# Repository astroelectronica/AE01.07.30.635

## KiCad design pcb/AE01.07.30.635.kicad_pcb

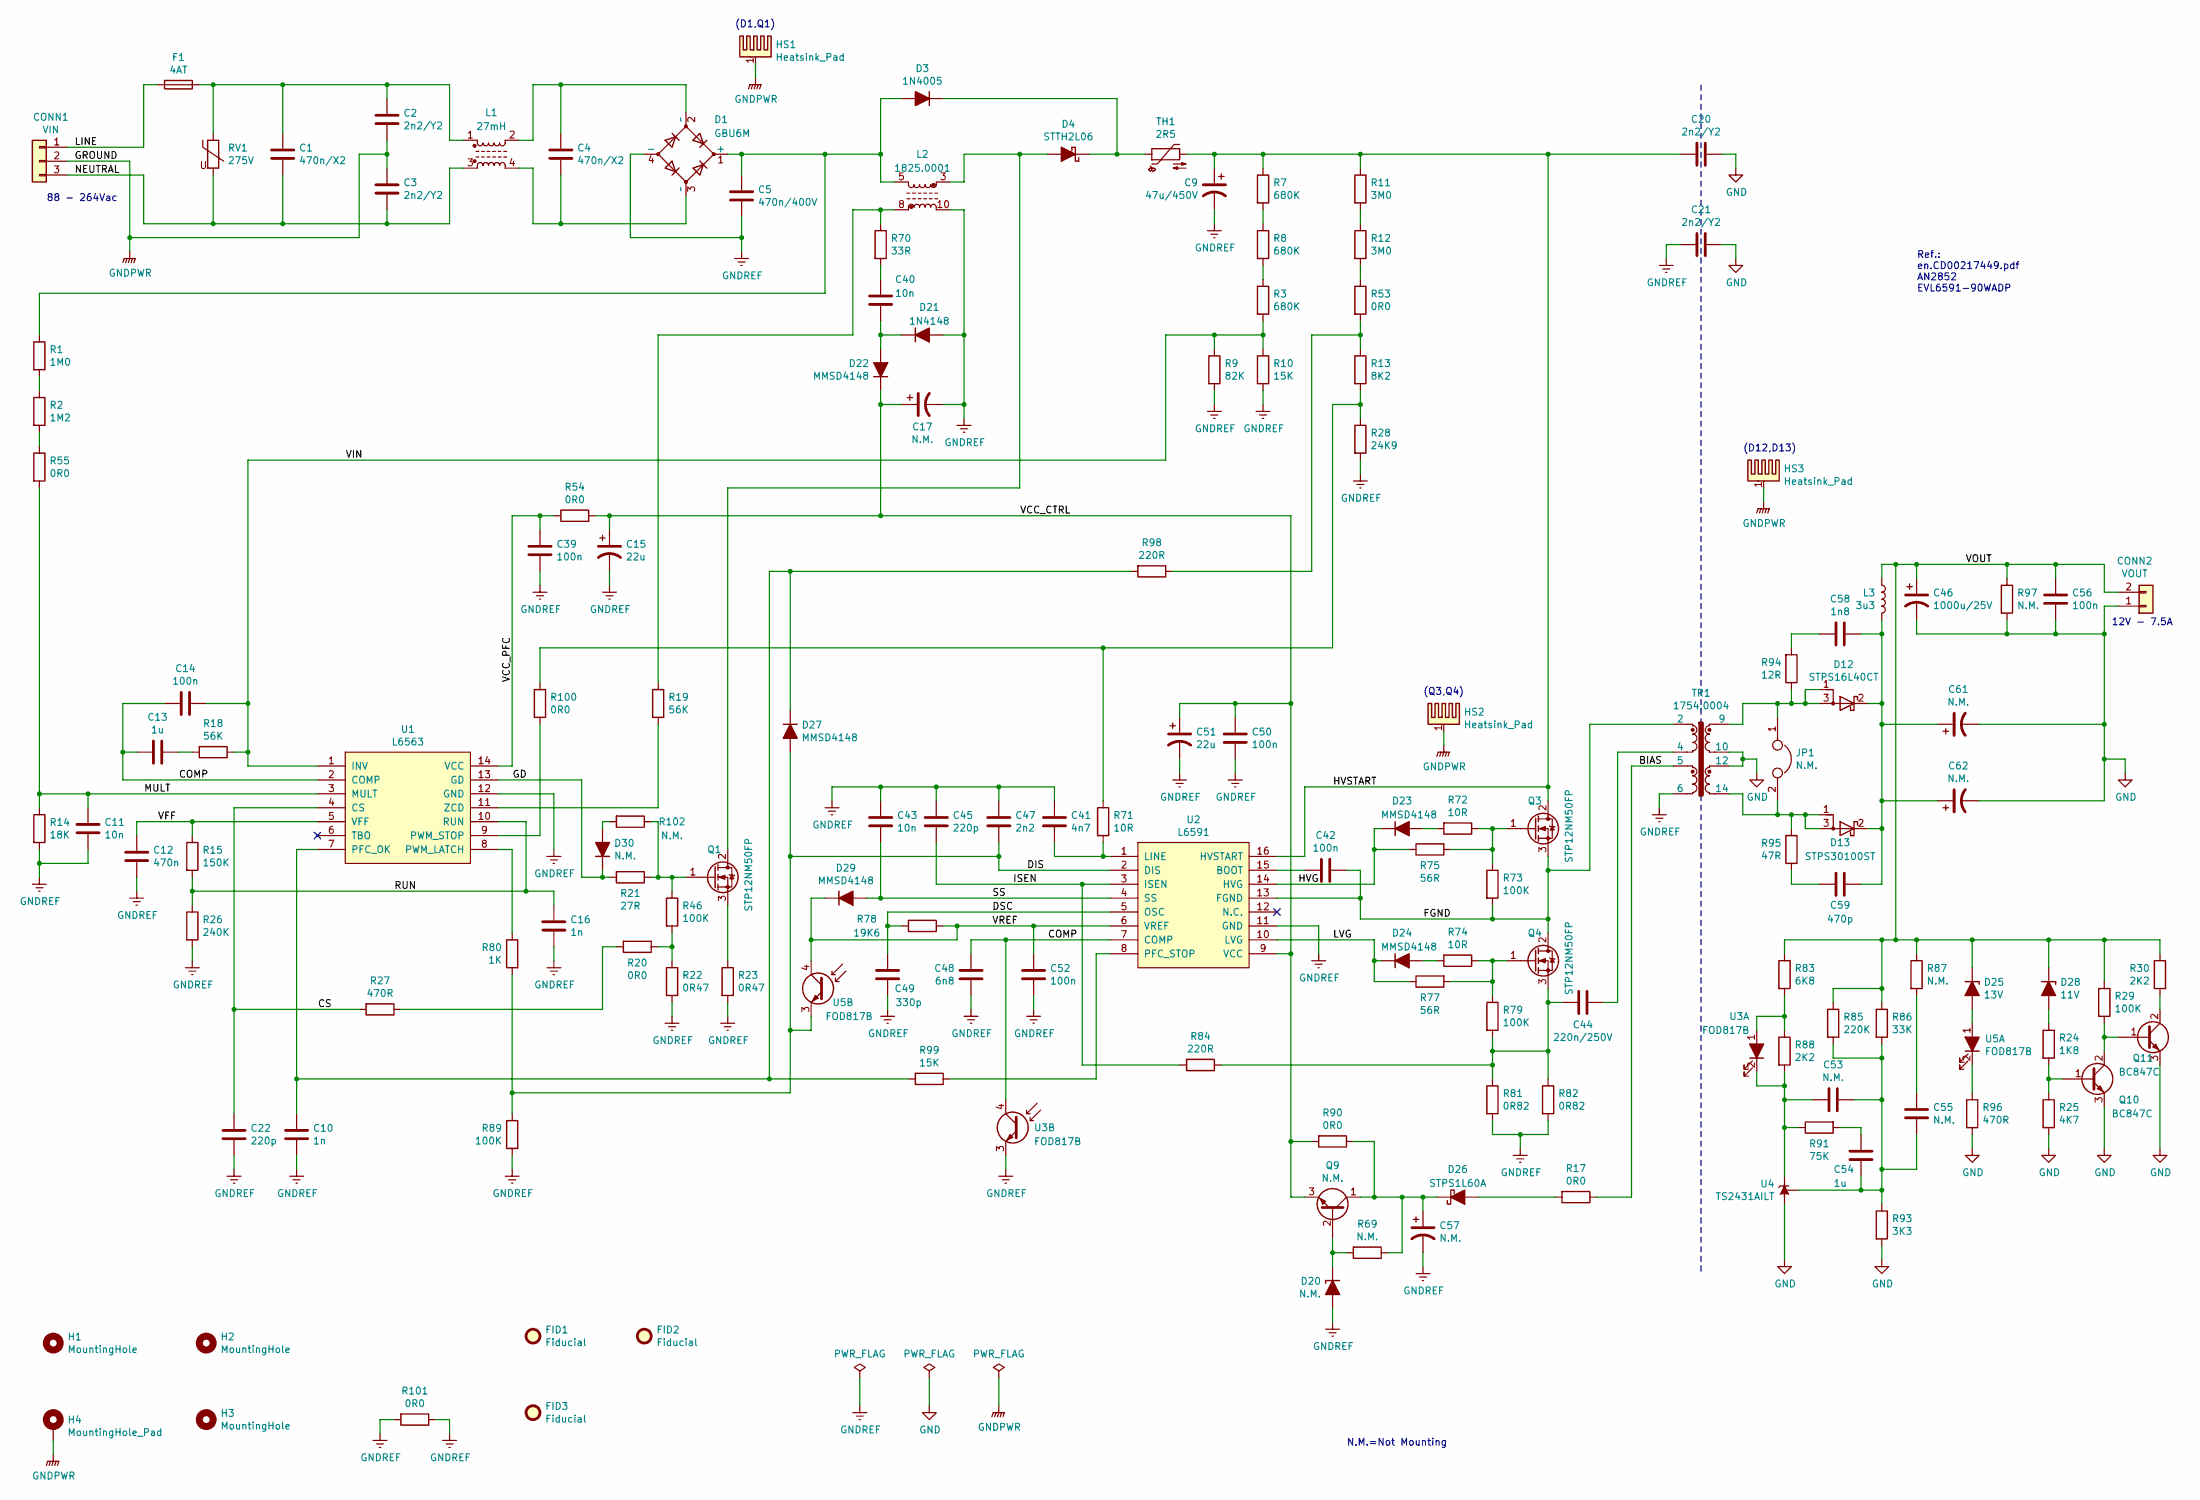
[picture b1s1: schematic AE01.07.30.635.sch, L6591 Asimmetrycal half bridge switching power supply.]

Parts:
C1, C4: 470n/X2; C_Rect_L18.0mm_W8.0mm_P15.00mm_FKS3_FKP3; MPN R46KI3470JH02M
C2, C3, C20, C21: 2n2/Y2; C_Disc_D8.0mm_W5.0mm_P7.50mm; MPN VY2222M31Y5VS63V7
C5: 470n/400V; C_Rect_L33.0mm_W13.0mm_P27.50mm_MKS4; MPN R76PR3470SE30J
C9: 47u/450V; CP_Radial_D18.0mm_P7.50mm; MPN EEU-ED2W470
C10, C16: 1n; C_0805_2012Metric; MPN C0805C102K5RACTU
C11, C40, C43: 10n; C_0805_2012Metric; MPN CC0805KRX7R9BB103
C12: 470n; C_0805_2012Metric; MPN CL21B474KAFNNNG
C13, C54: 1u; C_0805_2012Metric; MPN GCM21BR71E105KA56L
C14, C39, C42, C50, C52, C56: 100n; C_0805_2012Metric; MPN 08055C104KAT2A
C15, C51: 22u; CP_Radial_D5.0mm_P2.00mm; MPN UHE1H220MDD
C17, C57: N.M.; CP_Radial_D5.0mm_P2.00mm; MPN N.M.
C22, C45: 220p; C_0805_2012Metric; MPN C0805C221J5GACTU
C41: 4n7; C_0805_2012Metric; MPN CL21B472KB65PND
C44: 220n/250V; C_Rect_L18.0mm_W6.0mm_P15.00mm_FKS3_FKP3; MPN B32652A3224J000
C46: 1000u/25V; CP_Radial_D10.0mm_P5.00mm; MPN UVZ1E102MPD
C47: 2n2; C_0805_2012Metric; MPN CC0805KRX7R9BB222
C48: 6n8; C_0805_2012Metric; MPN CC0805KRX7R9BB682
C49: 330p; C_0805_2012Metric; MPN CC0805GRNPO9BN331
C53, C55: N.M.; C_0805_2012Metric; MPN N.M.
C58: 1n8; C_0805_2012Metric; MPN 08055C182KAT2A
C59: 470p; C_0805_2012Metric; MPN CC0805KRX7R9BB471
C61, C62: N.M.; CP_Radial_D10.0mm_P5.00mm; MPN N.M.
CONN1: VIN; TerminalBlock_Phoenix_MKDS-1,5-3-5.08_1x03_P5.08mm_Horizont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; MPN 1715734
CONN2: VOUT; TerminalBlock_Phoenix_MKDS-1,5-2-5.08_1x02_P5.08mm_Horizont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; MPN 1715721
D1: GBU6M; Diode_Bridge_Vishay_GBU; MPN GBU6M-E3/51
D3: 1N4005; D_DO-41_SOD81_P12.70mm_Horizontal; MPN 1N4005RLG
D4: STTH2L06; D_DO-41_SOD81_P12.70mm_Horizontal; MPN STTH2L06
D12: STPS16L40CT; TO-220-3_Vertical; MPN STPS16L40CT
D13: STPS30100ST; TO-220-3_Vertical; MPN STPS30100ST
D20, D30: N.M.; D_SOD-123; MPN N.M.
D21: 1N4148; D_DO-35_SOD27_P12.70mm_Horizontal; MPN 1N4148TR
D22, D23, D24, D27, D29: MMSD4148; D_SOD-123; MPN MMSD4148T1G
D25: 13V; D_SOD-123; MPN MMSZ5243C-E3-08
D26: STPS1L60A; D_SMA; MPN STPS2L60A
D28: 11V; D_SOD-123; MPN MMSZ5241C-E3-08
F1: 4AT; Fuseholder_TR5_Littelfuse_No560_No460; MPN 37214000411
FID1, FID2, FID3: Fiducial; Fiducial_0.5mm_Mask1mm
H1, H2, H3: MountingHole; MountingHole_3.2mm_M3_Pad_Via
H4: MountingHole_Pad; MountingHole_3.2mm_M3_Pad_Via
HS1, HS2, HS3: Heatsink_Pad
JP1: N.M.; PinHeader_1x02_P2.54mm_Vertical; MPN N.M.
L1: 27mH; Choke_Schaffner_RN142-04-33.1x32.5mm; MPN RN142-1.4-02-27M
L2: 1825.0001; RM14-LP_mF_1k_12-8_lo_rtg; MPN 1825.0001
L3: 3u3; L_Toroid_Vertical_L17.8mm_W9.7mm_P7.11mm_Pulse_B; MPN 2000-3R3-V-RC
Q1, Q3, Q4: STP12NM50FP; TO-220-3_Vertical; MPN STP12NM50FP
Q9: N.M.; SOT-23; MPN N.M.
Q10, Q11: BC847C; SOT-23; MPN BC847CLT1G
R1: 1M0; R_1206_3216Metric; MPN ERJ-8GEYJ105V
R2: 1M2; R_1206_3216Metric; MPN ERJ-8GEYJ125V
R3, R7, R8: 680K; R_Axial_DIN0204_L3.6mm_D1.6mm_P7.62mm_Horizontal; MPN MRS16000C6803FCT00
R9: 82K; R_0805_2012Metric; MPN RC0805FR-0782KL
R10: 15K; R_0805_2012Metric; MPN RC0805FR-0715KL
R11, R12: 3M0; R_Axial_DIN0414_L11.9mm_D4.5mm_P25.40mm_Horizontal; MPN HVR3700003004FR500
R13: 8K2; R_0805_2012Metric; MPN RC0805FR-078K2L
R14: 18K; R_1206_3216Metric; MPN ERJ-8GEYJ183V
R15: 150K; R_1206_3216Metric; MPN RK73B2BTTD154J
R17, R20, R53, R54, R55, R90, R100, R101: 0R0; R_1206_3216Metric; MPN RC1206JR-070RL
R18, R19: 56K; R_0805_2012Metric; MPN RC0805FR-0756KL
R21: 27R; R_1206_3216Metric; MPN RC1206JR-0727RL
R22, R23: 0R47; R_Axial_DIN0207_L6.3mm_D2.5mm_P15.24mm_Horizontal; MPN NFR25H0004707JR500
R24: 1K8; R_0805_2012Metric; MPN RC0805FR-071K8L
R25: 4K7; R_0805_2012Metric; MPN RC0805FR-074K7L
R26: 240K; R_0805_2012Metric; MPN ERJ-6ENF2403V
R27, R96: 470R; R_1206_3216Metric; MPN RC1206JR-07470RL
R28: 24K9; R_0805_2012Metric; MPN RC0805FR-0724K9L
R29, R46, R73, R79: 100K; R_0805_2012Metric; MPN RC0805FR-07100KL
R30: 2K2; R_1206_3216Metric; MPN RC1206FR-072K2L
R69, R87, R102: N.M.; R_0805_2012Metric; MPN N.M.
R70: 33R; R_1206_3216Metric; MPN RC1206FR-0733RL
R71: 10R; R_1206_3216Metric; MPN ERJ-8ENF10R0V
R72, R74: 10R; R_0805_2012Metric; MPN RMCF0805FT10R0
R75, R77: 56R; R_0805_2012Metric; MPN RC0805FR-0756RL
R78: 19K6; R_0805_2012Metric; MPN RC0805FR-0719K6L
R80: 1K; R_0805_2012Metric; MPN RC0805FR-071KL
R81, R82: 0R82; R_1206_3216Metric; MPN RL1206FR-070R82L
R83: 6K8; R_0805_2012Metric; MPN RC0805FR-076K8L
R84, R98: 220R; R_1206_3216Metric; MPN RC1206FR-07220RL
R85: 220K; R_0805_2012Metric; MPN RC0805FR-07220KL
R86: 33K; R_0805_2012Metric; MPN RC0805FR-0733KL
R88: 2K2; R_0805_2012Metric; MPN RC0805FR-072K2L
R89: 100K; R_1206_3216Metric; MPN RC1206FR-07100KL
R91: 75K; R_0805_2012Metric; MPN RC0805FR-0775KL
R93: 3K3; R_0805_2012Metric; MPN RC0805FR-073K3L
R94: 12R; R_1206_3216Metric; MPN RC1206FR-0712RL
R95: 47R; R_1206_3216Metric; MPN RC1206FR-0747RL
R97: N.M.; R_1206_3216Metric; MPN N.M.
R99: 15K; R_1206_3216Metric; MPN RC1206FR-0715KL
RV1: 275V; RV_Disc_D15.5mm_W5.4mm_P7.5mm; MPN B72214S2271K151
TH1: 2R5; C_Disc_D16.0mm_W5.0mm_P7.50mm; MPN B57237S0259M000
TR1: 1754.0004; ETD34_lr_h14_-1_rtg; MPN 1754.0004
U1: L6563; SOIC-14_3.9x8.7mm_P1.27mm; MPN L6563S
U2: L6591; SOIC-16_3.9x9.9mm_P1.27mm; MPN L6591TR
U3, U5: FOD817B; DIP-4_W7.62mm; MPN FOD817B
U4: TS2431AILT; SOT-23; MPN TS2431AILT

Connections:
/BIAS: R17.1, TR1.5
/COMP: C13.2, C14.2, C48.1, U1.2 (COMP), U2.7 (COMP), U3.4
/CS: C22.1, R27.2, U1.4 (CS)
/DIS: C47.2, D27.2 (A), R80.2, R89.1, U2.2 (DIS), U5.3
/DSC: C49.1, R78.2, U2.5 (OSC)
/FGND: C42.1, Q3.3 (S), Q4.2 (D), R73.2, TR1.2, U2.13 (FGND)
/GD: D30.1 (K), R21.2, U1.13 (GD)
/HVG: D23.1 (K), R75.1, U2.14 (HVG)
/HVSTART: C9.1, C20.2, Q3.2 (D), R7.1, R11.1, TH1.2, U2.16 (HVSTART)
/ISEN: C45.2, R84.2, U2.3 (ISEN)
/LINE: CONN1.1, F1.2
/LVG: D24.1 (K), R77.1, U2.10 (LVG)
/MULT: C11.1, R14.1, R55.2, U1.3 (MULT)
/NEUTRAL: C1.2, C3.2, CONN1.3, L1.3, RV1.2
/RUN: C16.1, R15.2, R26.1, U1.10 (RUN)
/SS: C43.2, D29.2 (A), U2.4 (SS)
/VCC_CTRL: C15.1, C17.1, C50.1, C51.1, D22.1 (K), Q9.3 (E), R54.2, R90.2, U2.9 (VCC)
/VCC_PFC: C39.1, R54.1, U1.14 (VCC)
/VFF: C12.1, R15.1, U1.5 (VFF)
/VIN: C14.1, R3.2, R9.1, R10.1, R18.1, U1.1 (INV)
/VOUT: C46.1, C56.1, CONN2.2, D25.1 (K), D28.1 (K), L3.2, R29.1, R30.1, R83.1, R85.1, R86.1, R87.1, R97.1
/VREF: C52.1, D29.1 (K), R78.1, U2.6 (VREF), U5.4
GND: C20.1, C21.1, C46.2, C56.2, C61.2, C62.2, CONN2.1, Q10.3 (E), Q11.3 (E), R25.2, R93.2, R96.2, R97.2, TR1.10, TR1.12, U4.3 (A)
GNDPWR: C2.2, C3.1, CONN1.2, H4.1, HS1.1, HS2.1, HS3.1
GNDREF: C5.2, C9.2, C10.2, C11.2, C12.2, C15.2, C16.2, C17.2, C21.2, C22.2, C39.2, C41.1, C43.1, C45.1, C47.1, C48.2, C49.2, C50.2, C51.2, C52.2, C57.2, D1.4 (-), D20.2 (A), D21.2 (A), L2.10, R9.2, R10.2, R14.2, R22.2, R23.2, R26.2, R28.2, R81.2, R82.2, R89.2, R101.1, R101.2, TR1.6, U1.12 (GND), U2.11 (GND), U3.3
unnamed: C1.1, C2.1, F1.1, L1.1, RV1.1
unnamed: C4.1, D1.2 (~~), L1.2
unnamed: C4.2, D1.3 (~~), L1.4
unnamed: C5.1, D1.1 (+), D3.2 (A), L2.5, R1.1
unnamed: C10.1, D27.1 (K), R98.2, R99.2, U1.7 (PFC_OK)
unnamed: C13.1, R18.2
unnamed: C40.1, R70.2
unnamed: C40.2, D21.1 (K), D22.2 (A)
unnamed: C41.2, R71.2, U2.1 (LINE)
unnamed: C42.2, U2.15 (BOOT)
unnamed: C44.1, TR1.4
unnamed: C44.2, Q4.3 (S), R79.2, R81.1, R82.1, R84.1
unnamed: C53.1, C54.1, C55.2, R85.2, R86.2, R93.1, U4.2 (REF)
unnamed: C53.2, R88.2, R91.1, U3.2, U4.1 (K)
unnamed: C54.2, R91.2
unnamed: C55.1, R87.2
unnamed: C57.1, D26.1 (K), Q9.1 (C), R69.1, R90.1
unnamed: C58.1, C59.1, C61.1, C62.1, D12.2 (K), D13.2 (K), L3.1
unnamed: C58.2, R94.2
unnamed: C59.2, R95.1
unnamed: D3.1 (K), D4.1 (K), TH1.1
unnamed: D4.2 (A), L2.3, Q1.2 (D)
unnamed: D12.1 (A), D12.3 (A), JP1.1, R94.1, TR1.9
unnamed: D13.1 (A), D13.3 (A), JP1.2, R95.2, TR1.14
unnamed: D20.1 (K), Q9.2 (B), R69.2
unnamed: D23.2 (A), R72.2
unnamed: D24.2 (A), R74.2
unnamed: D25.2 (A), U5.1
unnamed: D26.2 (A), R17.2
unnamed: D28.2 (A), R24.1
unnamed: D30.2 (A), R102.2
unnamed: L2.8, R19.1, R70.1
unnamed: Q1.1 (G), R21.1, R46.1, R102.1
unnamed: Q1.3 (S), R23.1
unnamed: Q3.1 (G), R72.1, R73.1, R75.2
unnamed: Q4.1 (G), R74.1, R77.2, R79.1
unnamed: Q10.1 (B), R24.2, R25.1
unnamed: Q10.2 (C), Q11.1 (B), R29.2
unnamed: Q11.2 (C), R30.2
unnamed: R1.2, R2.1
unnamed: R2.2, R55.1
unnamed: R3.1, R8.2
unnamed: R7.2, R8.1
unnamed: R11.2, R12.1
unnamed: R12.2, R53.1
unnamed: R13.1, R53.2, R98.1
unnamed: R19.2, U1.11 (ZCD)
unnamed: R20.1, R22.1, R46.2
unnamed: R20.2, R27.1
unnamed: R80.1, U1.8 (PWM_LATCH)
unnamed: R83.2, R88.1, U3.1
unnamed: R96.1, U5.2
unnamed: R99.1, U2.8 (PFC_STOP)
unnamed: R13.2, R28.1, R71.1, R100.1
unnamed: R100.2, U1.9 (PWM_STOP)

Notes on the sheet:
88 - 264Vac
12V - 7.5A
(Q3,Q4)
(D12,D13)
(D1,Q1)
N.M.=Not Mounting
Ref.: en.CD00217449.pdf AN2852 EVL6591-90WADP

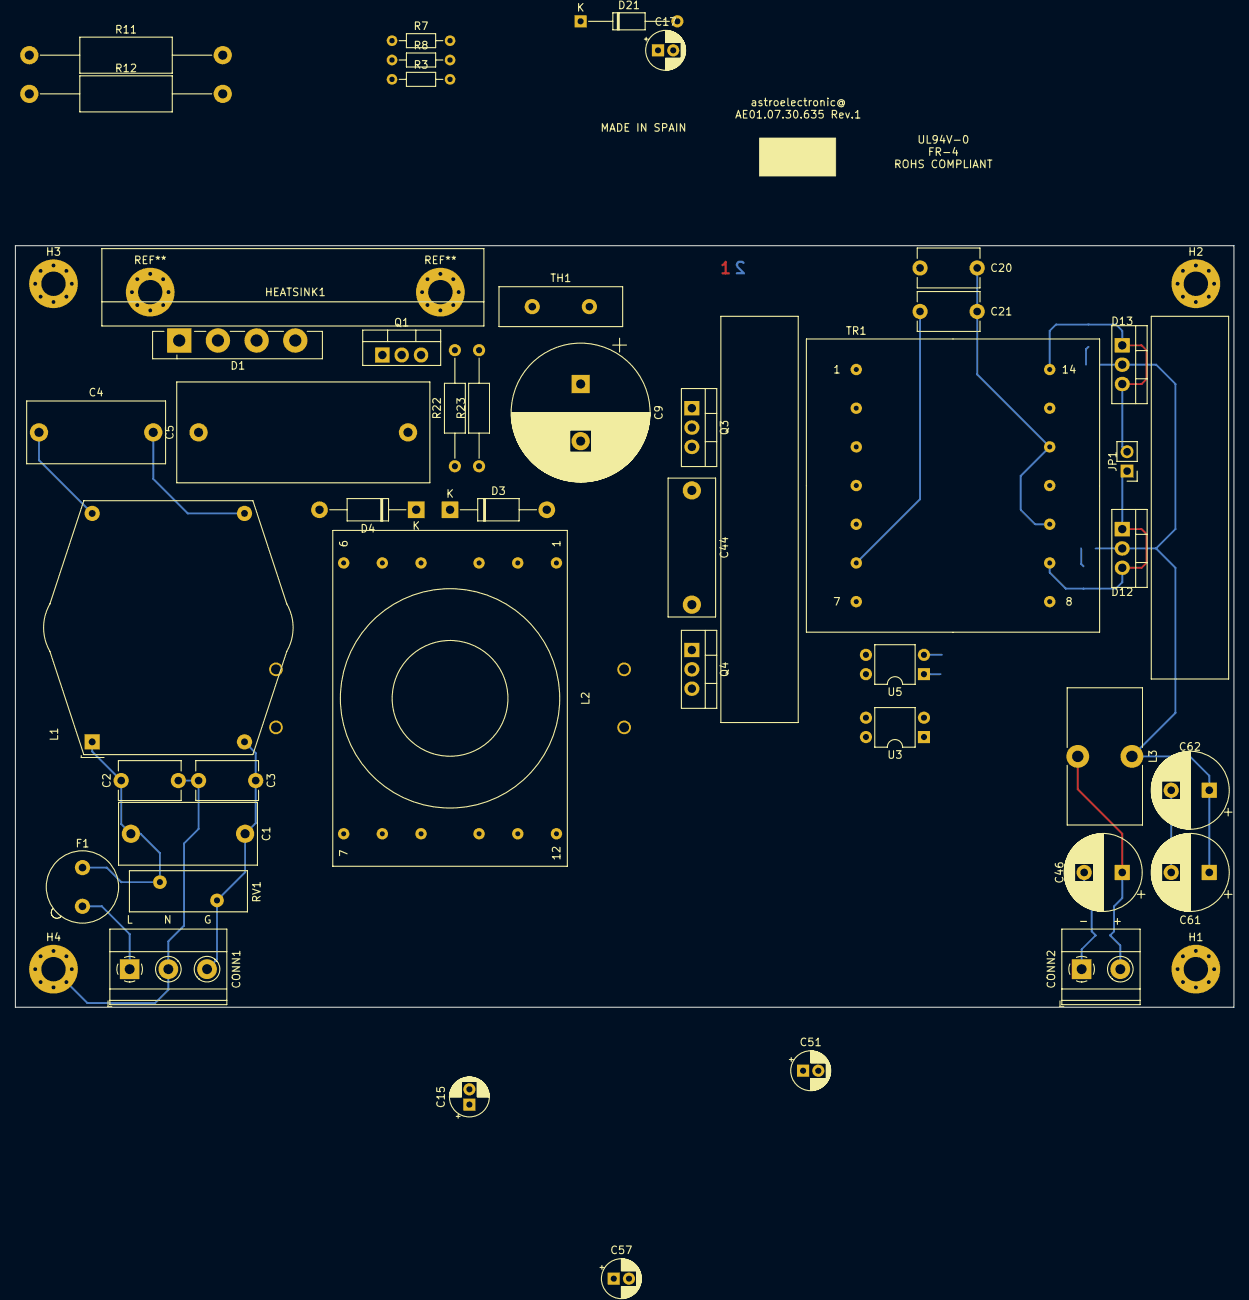
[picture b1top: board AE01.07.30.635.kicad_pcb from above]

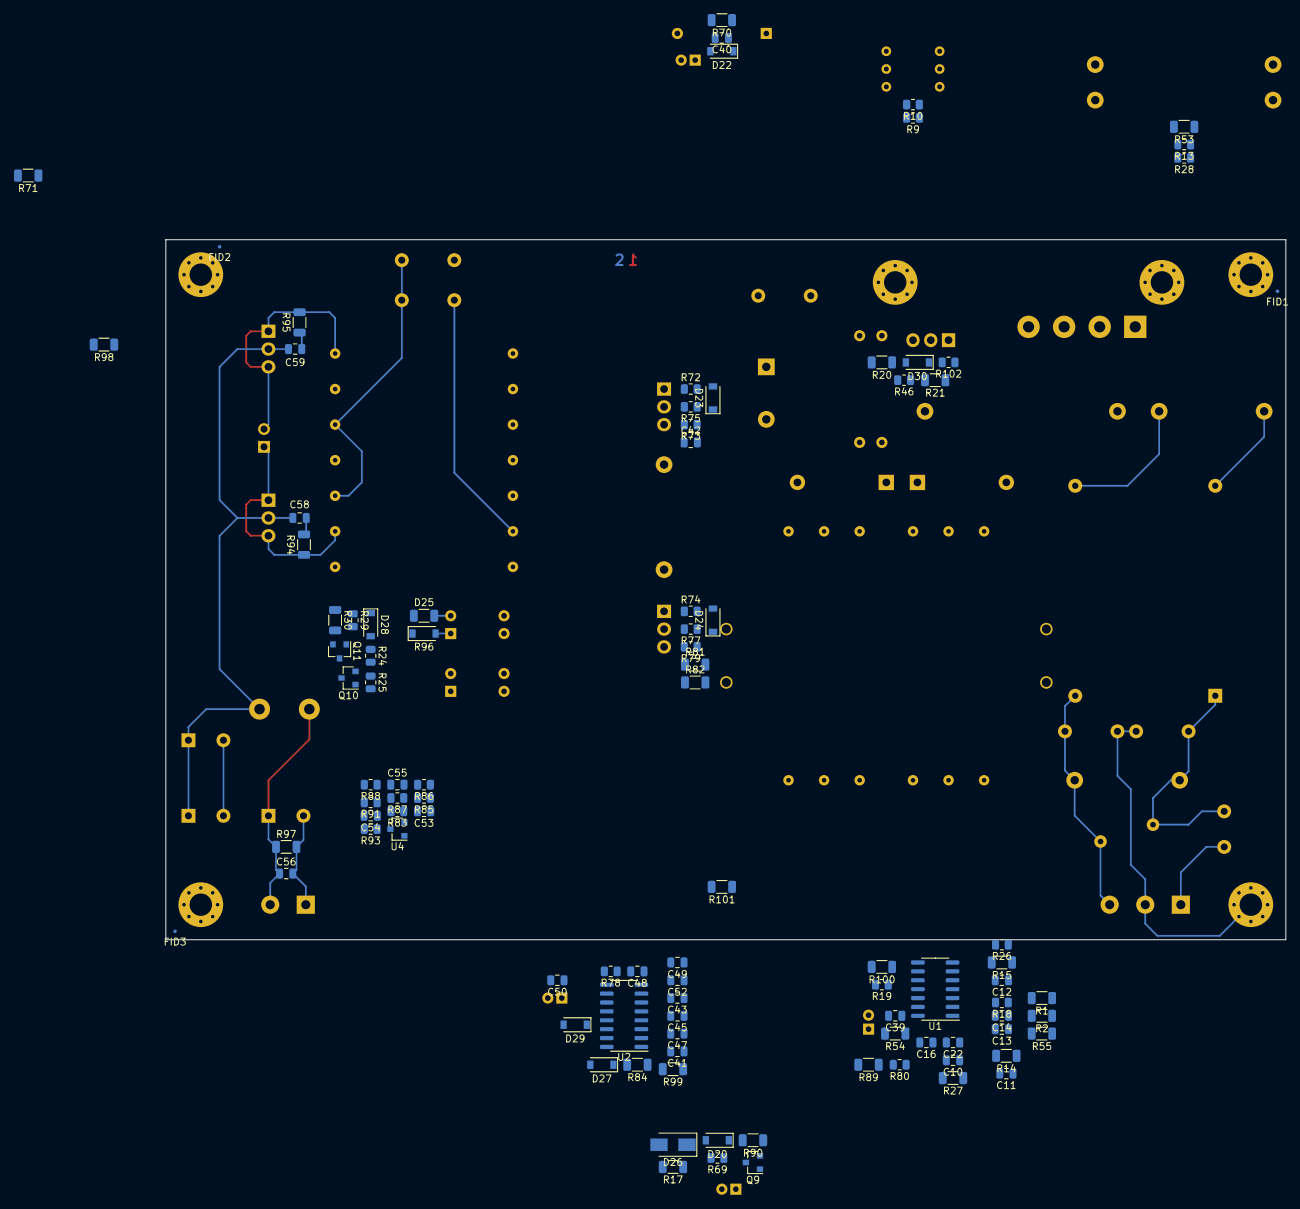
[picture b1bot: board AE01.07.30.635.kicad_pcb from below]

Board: 2 copper layers, 160.0 x 100.0 mm, 146 parts (98 on the bottom side), 80 nets.
